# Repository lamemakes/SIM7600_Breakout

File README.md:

# SIM7600 Breakout Board
*Needs a cooler name, huh?*

## TLDR
This project is a 4 layer PCB built around the SIM7600 to expose all of it's functionality to make it usable/hackable for a wide range of devices, with a form factor that can fit beautifully on a 30 row breadboard.

## Why?
The intent of this was to be able to experiment with 4G/LTE, learn more about how cellular networks function, and to eventually build something that utilizes these networks along with the SIM7600.

## KiCAD
The required symbols/footprints/3D models can be found in the directories: lib_sch/sim7600_breakout.pretty/3dmodels respectively.

## Usage Pre-Requisites
- A fully assembled lamemakes SIM7600 Breakout Board
- Antennas for respective purposes
    - 50Ω passive LTE/4G w/ U.FL connector
    - 50Ω **active/powered** GPS/GNSS w/ U.FL connector)
- An activated Nano SIM card
    - Carrier _shouldn't_ matter, see **IMEI** section
- Device that supports some form of serial communication
    - UART, I2C, and SPI are all supported.
- _(Optional)_ Wired headphones, ideally with about a 35Ω impedence.

## Usage 
The breakout board can be initialized by connecting +3.3v to the +3v3 pin, and ground to the GND pin. Then, turn the module on by pulling the PKEY HIGH.

## Pics

*Schematic*

*PCB*

## Notes
- **Be a good neighbor on the RF spectrum!** There is certainly a lot of grey area when it comes to legality and LTE/carrier service, so be conscientious - stay within local law. 
- As of writing (12/09/22) this has yet to be constructed. The OSH Park order is out, but the SIM7600G-H is backordered at Digikey along with literally every other SIM7600 model. Hoping for a restock before the new year.
- Contribute! This is my first real RF/4G PCB, so if you see somewhere that could be improved feel free to raise an issue or put up a PR.
- As this is assembled and tinkered with, this README will be immensely updated for better usage instructions.
- It's clear the language barrier is an issue when it comes to the SIM7600 docs, but these resources helped me out a ton:
    - [Xinyuan LilyGO/T](https://github.com/Xinyuan-LilyGO/T-SIM7600X)
    - [CircuitMess Ringo](https://github.com/CircuitMess/CircuitMess-Ringo) <- such a cool project, look to do something very similar moving forward
    - [Waveshare SIM7600 HAT docs](https://www.waveshare.com/wiki/SIM7600E-H_4G_HAT)

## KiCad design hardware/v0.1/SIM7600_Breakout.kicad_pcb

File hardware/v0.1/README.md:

# SIM7600 Breakout Board Hardware

## BOM

A list of the parts used & where they can be found

| Part No.            | Ref Des                                            | Link                                                                                                         | Quantity | Notes                         |
| ------------------- | -------------------------------------------------- | ------------------------------------------------------------------------------------------------------------ | -------- | ----------------------------- |
| 2137160001          | `J5`                                               | [Digikey](https://www.digikey.com/en/products/detail/molex/2137160001/13662558)                              | 1        | USB C 2.0 Receptacle          |
| SIM7600G R2         | `U3`                                               | [Digikey](https://www.digikey.com/en/products/detail/simcom-wireless-solutions-limited/SIM7600G-R2/15841466) | 1        | SIMCom Wireless LTE Module    |
| NAU8810YG           | `U4`                                               | [Digikey](https://www.digikey.com/en/products/detail/nuvoton-technology-corporation/NAU8810YG/4271435)       | 1        | Audio Codec                   |
| NVT2008PW,118       | `U1`, `U2`                                         | [Digikey](https://www.digikey.com/en/products/detail/nxp-usa-inc/nvt2008pw-118/2530413)                      | 2        | Serial Logic Shifter          |
| SIM8060-6-0-14-00-A | `J1`                                               | [Digikey](https://www.digikey.com/en/products/detail/gct/sim8060-6-0-14-00-a/9859630)                        | 1        | Nano SIM Card Holder          |
| MMBT3904L RFG       | `Q1`                                               | [Digikey](https://www.digikey.com/en/products/detail/taiwan-semiconductor-corporation/mmbt3904l-rfg/7357838) | 1        | NPN BJT for SIM7600 Power Key |
| PESD2V0Y1BSFYL      | `D5`                                               | [Digikey](https://www.digikey.com/en/products/detail/nexperia-usa-inc/pesd2v0y1bsfyl/8628181)                | 1        | TVS Diode                     |
| ESD9L5.0ST5G        | `D3`, `D4`                                         | [Digikey](https://www.digikey.com/en/products/detail/onsemi/ESD9L5-0ST5G/1693175)                            | 2        | TVS Diode (USB Data)          |
| U.FL-R-SMT-1(01)    | `J6`, `J7`, `J8`                                   | [Digikey](https://www.digikey.com/en/products/detail/hirose-electric-co-ltd/U-FL-R-SMT-1-01/3978494)         | 3        | Male U.FL 50Ω Receptacle      |
| MJ-3502N            | `J3`                                               | [Digikey](https://www.digikey.com/en/products/detail/cui-devices/MJ-3502N/281266)                            | 1        | 3.5mm Headphone Phone Jack    |
| AOM-4542P-R         | `MK1`                                              | [Digikey](https://www.digikey.com/en/products/detail/pui-audio-inc/AOM-4542P-R/1745490)                      | 1        | Analog Condenser Microphone   |
| C0603C220J5GACTU    | `C1`, `C2`, `C3`                                   | [Digikey](https://www.digikey.com/en/products/detail/kemet/C0603C220J5GACTU/411055)                          | 3        | 22pF caps                     |
| CL10B104KO8NNNC     | `C4`, `C9`, `C10`, `C12`                           | [Digikey](https://www.digikey.com/en/products/detail/samsung-electro-mechanics/CL10B104KO8NNNC/3886663)      | 1        | 0.1uF cap                     |
| CL10A106MQ8NNNC     | `C5`                                               | [Digikey](https://www.digikey.com/en/products/detail/samsung-electro-mechanics/CL10A106MQ8NNNC/3886777)      | 1        | 10uF cap                      |
| CL10A475KP8NNNC     | `C6`, `C23`, `C24`, `C25`, `C26`                   | [Digikey](https://www.digikey.com/en/products/detail/samsung-electro-mechanics/CL10A475KP8NNNC/3886702)      | 1        | 4.7uF cap                     |
| CL10B105KP8NNNC     | `C7`, `C8`                                         | [Digikey](https://www.digikey.com/en/products/detail/samsung-electro-mechanics/CL10B105KP8NNNC/3887604)      | 1        | 1uF cap                       |
| CL10C330JB8NNNC     | `C27`                                              | [Digikey](https://www.digikey.com/en/products/detail/samsung-electro-mechanics/CL10C330JB8NNNC/3886728)      | 1        | 33pF cap                      |
| GRM188R60J476ME15D  | `C19`, `C22`                                       | [Digikey](https://www.digikey.com/en/products/detail/murata-electronics/GRM188R60J476ME15D/5877410)          | 2        | 47uF cap                      |
| 150120RS75000       | `D1`, `D2`                                         | [Digikey](https://www.digikey.com/en/products/detail/w%C3%BCrth-elektronik/150120RS75000/4489939)            | 2        | Red LED                       |
| M20-9990245         | `J2`                                               | [Digikey](https://www.digikey.com/en/products/detail/harwin-inc/M20-9990245/3728225)                         | 1        | 1x2 2.54mm male header pins   |
| BSCH0010050547NJCP  | `L1`                                               | [Digikey](https://www.digikey.com/en/products/detail/pulse-electronics/BSCH0010050547NJCP/10508660)          | 1        | 47nH inductor                 |
| RC0201JR-0747KL     | `R1`, `R2`, `R3`, `R9`, `R10`, `R11`, `R12`, `R13` | [Digikey](https://www.digikey.com/en/products/detail/yageo/RC0201JR-0747KL/1948954)                          | 8        | 47kΩ resistor                 |
| RC0201FR-074K7L     | `R4`, `R8`, `R19`, `R20`, `R21`                    | [Digikey](https://www.digikey.com/en/products/detail/yageo/RC0201FR-074K7L/1948894)                          | 5        | 4k7Ω resistor                 |
| RC0201JR-075K1L     | `R5`, `R24`                                        | [Digikey](https://www.digikey.com/en/products/detail/yageo/RC0201JR-075K1L/5280770)                          | 1        | 5k1Ω resistor                 |
| RC0201FR-0722RL     | `R6`, `R7`                                         | [Digikey](https://www.digikey.com/en/products/detail/yageo/RC0201FR-0722RL/5280378)                          | 2        | 22Ω resistor                  |
| RC0201FR-071K3L     | `R14`, `R15`                                       | [Digikey](https://www.digikey.com/en/products/detail/yageo/RC0201FR-071K3L/3202386)                          | 2        | 1k3Ω resistor                 |
| RC0201FR-07390RL    | `R16`, `R17`                                       | [Digikey](https://www.digikey.com/en/products/detail/yageo/RC0201FR-07390RL/3202404)                         | 2        | 390Ω resistor                 |
| RC0201FR-0710RL     | `R18`                                              | [Digikey](https://www.digikey.com/en/products/detail/yageo/RC0201FR-0710RL/1948874)                          | 1        | 10Ω resistor                  |
| RC0201FR-072K2L     | `R22`, `R23`                                       | [Digikey](https://www.digikey.com/en/products/detail/yageo/RC0201FR-072K2L/5280432)                          | 2        | 2k2Ω resistor                 |

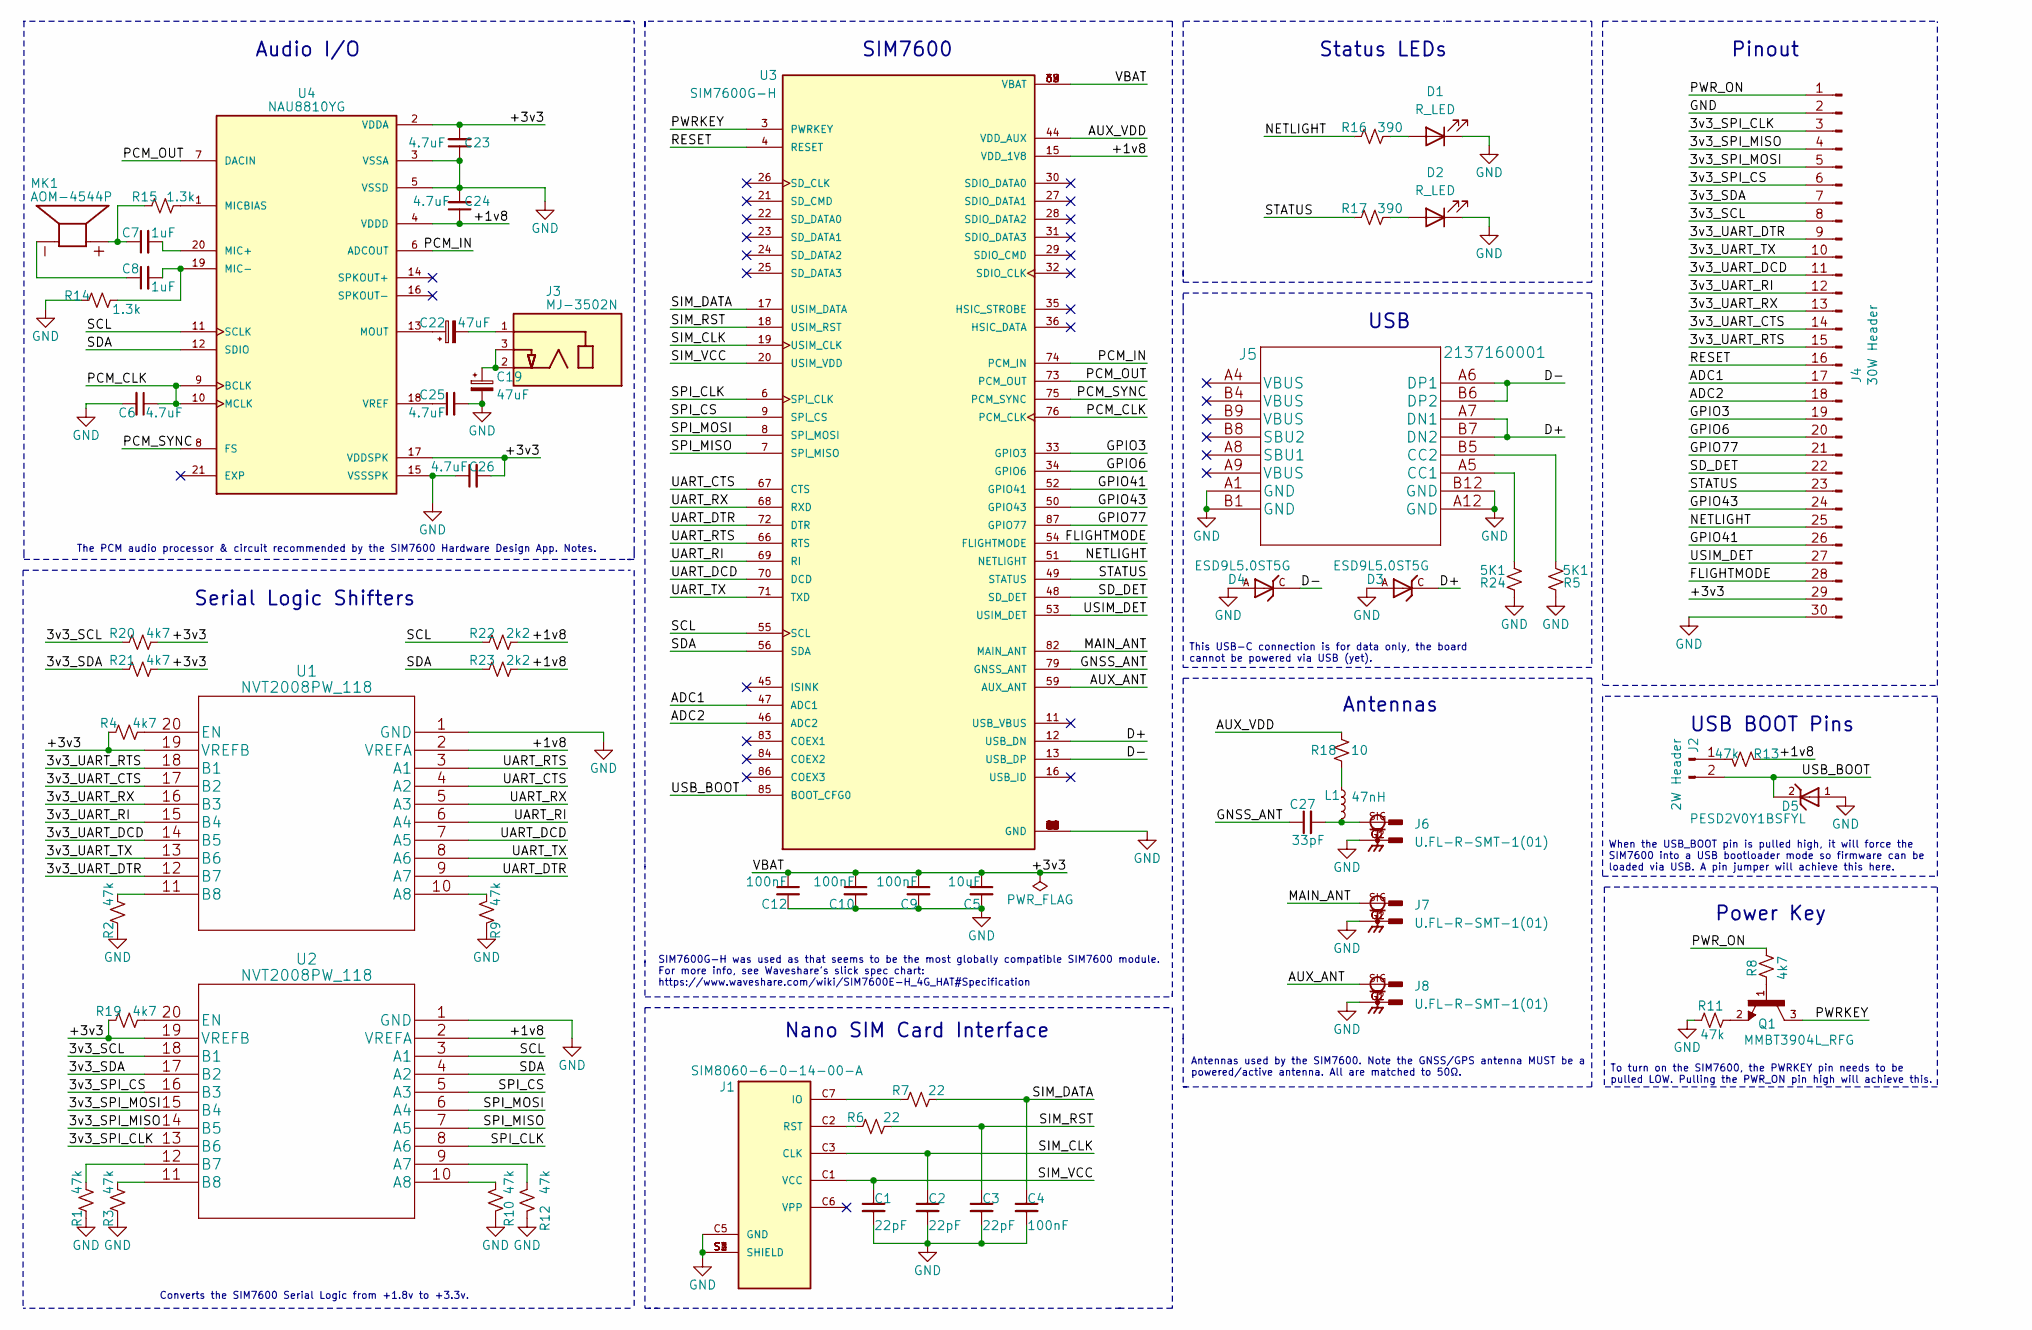
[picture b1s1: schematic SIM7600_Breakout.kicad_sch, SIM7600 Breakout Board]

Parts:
C1, C2, C3: 22pF; C_0603_1608Metric_Pad1.08x0.95mm_HandSolder
C4, C9, C10, C12: 100nF; C_0603_1608Metric_Pad1.08x0.95mm_HandSolder
C5: 10uF; C_0603_1608Metric_Pad1.08x0.95mm_HandSolder
C6, C23, C24, C25, C26: 4.7uF; C_0603_1608Metric_Pad1.08x0.95mm_HandSolder
C7, C8: 1uF; C_0603_1608Metric_Pad1.08x0.95mm_HandSolder
C19, C22: 47uF; 865080543009
C27: 33pF; C_0603_1608Metric_Pad1.08x0.95mm_HandSolder
D1, D2: R_LED; LED_1206_3216Metric_Pad1.42x1.75mm_HandSolder
D3, D4: ESD9L5.0ST5G; DIOM1006X40N; PARTREV 7
D5: PESD2V0Y1BSFYL; PARTREV 7
J1: SIM8060-6-0-14-00-A; GCT_SIM8060-6-0-14-00-A
J2: 2W Header; PinHeader_1x02_P2.54mm_Vertical
J3: MJ-3502N; CUI_MJ-3502N; PART_REV A
J4: 30W Header; PinHeader_1x30_P2.54mm_Vertical
J5: 2137160001; 2137160001-USB-C
J6, J7, J8: U.FL-R-SMT-1(01); HIROSE_U.FL-R-SMT-1(01); PARTREV Jul.1.2022
L1: 47nH; IND_LQP02HQ47NH02E
MK1: AOM-4544P; MIC_AOM-4544P-NF-R; PARTREV B
Q1: MMBT3904L_RFG; SOT95P237X112-3N; PARTREV I2001
R1, R2, R3, R9, R10, R11, R12, R13: 47k; R_0201_0603Metric_Pad0.64x0.40mm_HandSolder
R4, R8, R19, R20, R21: 4k7; R_0201_0603Metric_Pad0.64x0.40mm_HandSolder
R5, R24: 5K1; R_0201_0603Metric_Pad0.64x0.40mm_HandSolder
R6, R7: 22; R_0201_0603Metric_Pad0.64x0.40mm_HandSolder
R14, R15: 1.3k; R_0201_0603Metric_Pad0.64x0.40mm_HandSolder
R16, R17: 390; R_0201_0603Metric_Pad0.64x0.40mm_HandSolder
R18: 10; R_0201_0603Metric_Pad0.64x0.40mm_HandSolder
R22, R23: 2k2; R_0201_0603Metric_Pad0.64x0.40mm_HandSolder
U1, U2: NVT2008PW_118
U3: SIM7600G-H; IC_SIM7600E-H; PARTREV 1.01
U4: NAU8810YG; QFN50P400X400X80-21N; PARTREV 2.8

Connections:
/3v3_SCL: J4.8, R20.1, U2.18 (B1)
/3v3_SDA: J4.7, R21.1, U2.17 (B2)
/3v3_SPI_CLK: J4.3, U2.13 (B6)
/3v3_SPI_CS: J4.6, U2.16 (B3)
/3v3_SPI_MISO: J4.4, U2.14 (B5)
/3v3_SPI_MOSI: J4.5, U2.15 (B4)
/3v3_UART_CTS: J4.14, U1.17 (B2)
/3v3_UART_DCD: J4.11, U1.14 (B5)
/3v3_UART_DTR: J4.9, U1.12 (B7)
/3v3_UART_RI: J4.12, U1.15 (B4)
/3v3_UART_RTS: J4.15, U1.18 (B1)
/3v3_UART_RX: J4.13, U1.16 (B3)
/3v3_UART_TX: J4.10, U1.13 (B6)
/+1v8: C24.1, R13.1, R22.2, R23.2, U1.2 (VREFA), U2.2 (VREFA), U3.15 (VDD_1V8), U4.4 (VDDD)
/+3v3: C5.1, C9.1, C10.1, C12.1, C23.2, C26.2, J4.29, R4.1, R19.1, R20.2, R21.2, U1.19 (VREFB), U2.19 (VREFB), U3.38 (VBAT), U3.39 (VBAT), U3.62 (VBAT), U3.63 (VBAT), U4.2 (VDDA), U4.17 (VDDSPK)
/ADC1: J4.17, U3.47 (ADC1)
/ADC2: J4.18, U3.46 (ADC2)
/AUX_ANT: J8.SIG, U3.59 (AUX_ANT)
/AUX_VDD: R18.2, U3.44 (VDD_AUX)
/D+: D3.C, J5.A7 (DN1), J5.B7 (DN2), U3.12 (USB_DN)
/D-: D4.C, J5.A6 (DP1), J5.B6 (DP2), U3.13 (USB_DP)
/FLIGHTMODE: J4.28, U3.54 (FLIGHTMODE)
/GNSS_ANT: C27.1, U3.79 (GNSS_ANT)
/GPIO3: J4.19, U3.33 (GPIO3)
/GPIO6: J4.20, U3.34 (GPIO6)
/GPIO41: J4.26, U3.52 (GPIO41)
/GPIO43: J4.24, U3.50 (GPIO43)
/GPIO77: J4.21, U3.87 (GPIO77)
/MAIN_ANT: J7.SIG, U3.82 (MAIN_ANT)
/NETLIGHT: J4.25, R16.1, U3.51 (NETLIGHT)
/PCM_CLK: C6.1, U3.76 (PCM_CLK), U4.9 (BCLK), U4.10 (MCLK)
/PCM_IN: U3.74 (PCM_IN), U4.6 (ADCOUT)
/PCM_OUT: U3.73 (PCM_OUT), U4.7 (DACIN)
/PCM_SYNC: U3.75 (PCM_SYNC), U4.8 (FS)
/PWRKEY: Q1.3, U3.3 (PWRKEY)
/PWR_ON: J4.1, R8.2
/RESET: J4.16, U3.4 (RESET)
/SCL: R22.1, U2.3 (A1), U3.55 (SCL), U4.11 (SCLK)
/SDA: R23.1, U2.4 (A2), U3.56 (SDA), U4.12 (SDIO)
/SD_DET: J4.22, U3.48 (SD_DET)
/SIM_CLK: C2.1, J1.C3 (CLK), U3.19 (USIM_CLK)
/SIM_DATA: C4.1, R7.2, U3.17 (USIM_DATA)
/SIM_RST: C3.1, R6.2, U3.18 (USIM_RST)
/SIM_VCC: C1.1, J1.C1 (VCC), U3.20 (USIM_VDD)
/SPI_CLK: U2.8 (A6), U3.6 (SPI_CLK)
/SPI_CS: U2.5 (A3), U3.9 (SPI_CS)
/SPI_MISO: U2.7 (A5), U3.7 (SPI_MISO)
/SPI_MOSI: U2.6 (A4), U3.8 (SPI_MOSI)
/STATUS: J4.23, R17.1, U3.49 (STATUS)
/UART_CTS: U1.4 (A2), U3.67 (CTS)
/UART_DCD: U1.7 (A5), U3.70 (DCD)
/UART_DTR: U1.9 (A7), U3.72 (DTR)
/UART_RI: U1.6 (A4), U3.69 (RI)
/UART_RTS: U1.3 (A1), U3.66 (RTS)
/UART_RX: U1.5 (A3), U3.68 (RXD)
/UART_TX: U1.8 (A6), U3.71 (TXD)
/USB_BOOT: D5.2, J2.2, U3.85 (BOOT_CFG0)
/USIM_DET: J4.27, U3.53 (USIM_DET)
GND: C1.2, C2.2, C3.2, C4.2, C5.2, C6.2, C9.2, C10.2, C12.2, C19.2, C23.1, C24.2, C25.2, C26.1, D1.1 (K), D2.1 (K), D3.A, D4.A, D5.1, J1.C5 (GND), J1.S1 (SHIELD), J1.S2 (SHIELD), J1.S3 (SHIELD), J1.S4 (SHIELD), J4.2, J4.30, J5.A1 (GND), J5.A12 (GND), J5.B1 (GND), J5.B12 (GND), J6.G1, J6.G2, J7.G1, J7.G2, J8.G1, J8.G2, R1.1, R2.1, R3.1, R5.1, R9.1, R10.1, R11.1, R12.1, R14.1, R24.1, U1.1 (GND), U2.1 (GND), U3.1 (GND), U3.2 (GND), U3.5 (GND), U3.10 (GND), U3.14 (GND), U3.37 (GND), U3.40 (GND), U3.41 (GND), U3.43 (GND), U3.57 (GND), U3.58 (GND), U3.60 (GND), U3.61 (GND), U3.64 (GND), U3.65 (GND), U3.77 (GND), U3.78 (GND), U3.80 (GND), U3.81 (GND), U4.3 (VSSA), U4.5 (VSSD), U4.15 (VSSSPK)
unnamed: C7.1, MK1.P, R15.1
unnamed: C8.1, MK1.N
unnamed: C19.1, J3.2, J3.3
unnamed: C22.2, J3.1
unnamed: C27.2, J6.SIG, L1.2
unnamed: D1.2 (A), R16.2
unnamed: D2.2 (A), R17.2
unnamed: J1.C7 (IO), R7.1
unnamed: J1.C2 (RST), R6.1
unnamed: J2.1, R13.2
unnamed: J5.A5 (CC1), R24.2
unnamed: J5.B5 (CC2), R5.2
unnamed: L1.1, R18.1
unnamed: Q1.1, R8.1
unnamed: Q1.2, R11.2
unnamed: R9.2, U1.10 (A8)
unnamed: R2.2, U1.11 (B8)
unnamed: R4.2, U1.20 (EN)
unnamed: R12.2, U2.9 (A7)
unnamed: R10.2, U2.10 (A8)
unnamed: R1.2, U2.12 (B7)
unnamed: R3.2, U2.11 (B8)
unnamed: R19.2, U2.20 (EN)
unnamed: C7.2, U4.20 (MIC+)
unnamed: C8.2, R14.2, U4.19 (MIC-)
unnamed: R15.2, U4.1 (MICBIAS)
unnamed: C22.1, U4.13 (MOUT)
unnamed: C25.1, U4.18 (VREF)

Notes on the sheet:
USB BOOT Pins
Nano SIM Card Interface
The PCM audio processor & circuit recommended by the SIM7600 Hardware Design App. Notes.
SIM7600G-H was used as that seems to be the most globally compatible SIM7600 module. For more info, see Waveshare's slick spec chart: https://www.waveshare.com/wiki/SIM7600E-H_4G_HAT#Specification
SIM7600
Antennas used by the SIM7600. Note the GNSS/GPS antenna MUST be a powered/active antenna. All are matched to 50Ω.
Power Key
Audio I/O
Converts the SIM7600 Serial Logic from +1.8v to +3.3v.
This USB-C connection is for data only, the board cannot be powered via USB (yet).
To turn on the SIM7600, the PWRKEY pin needs to be pulled LOW. Pulling the PWR_ON pin high will achieve this.
Antennas
Pinout
USB
Serial Logic Shifters
Status LEDs
When the USB_BOOT pin is pulled high, it will force the SIM7600 into a USB bootloader mode so firmware can be loaded via USB. A pin jumper will achieve this here.

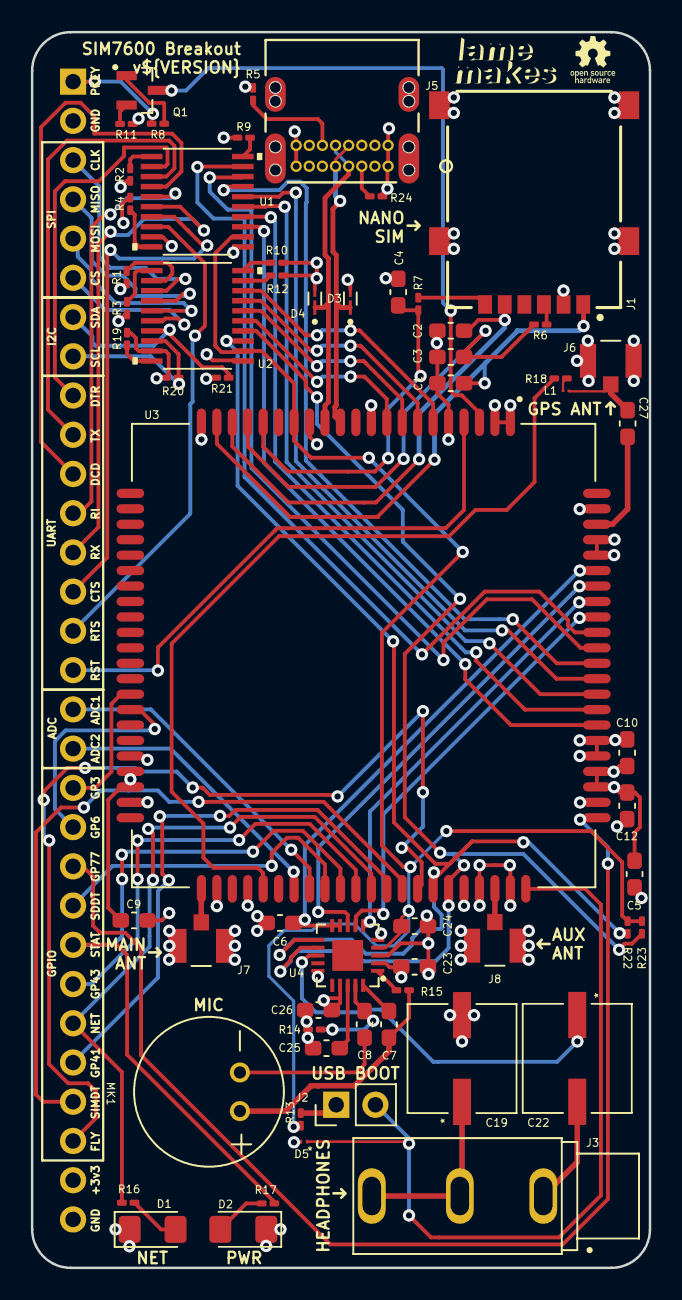
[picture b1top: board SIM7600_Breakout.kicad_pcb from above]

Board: 4 copper layers, 40.0 x 80.0 mm, 62 parts (1 on the bottom side), 87 nets.

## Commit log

2022-12-09 Initial board commit
2022-12-09 Removed backups + updated gitignore
2022-12-09 Documentation updates + pics
2022-12-09 PCB label update
2022-12-20 Minor fixes
2023-11-28 Update README.md for archival
2024-07-26 Unarchived repo
2024-08-01 Updated models to use USB-C & added a BOM to track parts/links
2024-08-03 Added mic to BOM
2024-08-09 Added USB C to schematic & half assed putting it on the PCB
2024-11-18 Cleaning up USB-C addition
2024-11-19 "it's USB 2.0 I don't care", logo updates
2024-12-02 Updated README & added KiCad image generator action
2024-12-02 Update KiCad Image
2024-12-27 Added BOM and updated gitignore
2024-12-30 Added project wide versioning, cleaned up & added PCB text
2024-12-30 Updated image generation workflow

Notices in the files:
parts and their libraries:
Copyright 2021 Accelerated Designs. All rights reserved.
Copyright 2016 Accelerated Designs. All rights reserved.
